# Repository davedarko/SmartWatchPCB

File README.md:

# SmartWatchPCB

work in progress, this is just setup to jump between computers n stuff.

I'm replacing the PCB of a cool watch from aliexpress

more on the project here
https://hackaday.io/project/180832-new-pcb-for-calculator-watch

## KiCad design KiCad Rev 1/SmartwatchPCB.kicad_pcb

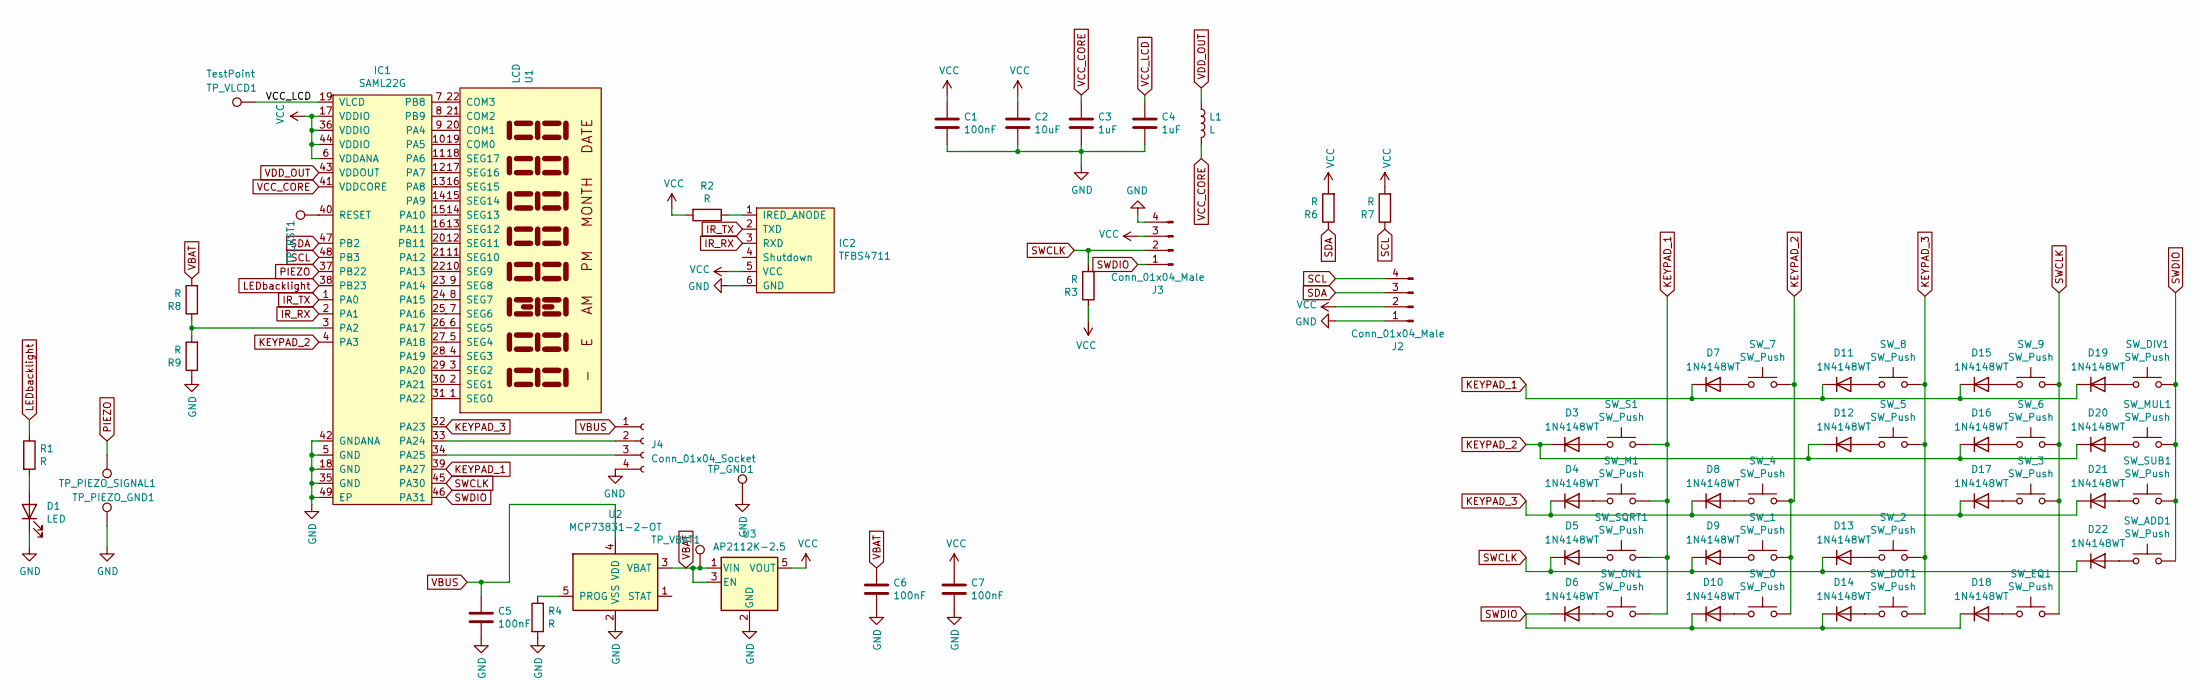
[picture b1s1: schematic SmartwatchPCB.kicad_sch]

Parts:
C1, C5, C6, C7: 100nF; C_0603_1608Metric
C2: 10uF; C_0603_1608Metric
C3, C4: 1uF; C_0603_1608Metric
D1: LED; LED_0603_1608Metric_Castellated
D3, D4, D5, D6, D7, D8, D9, D10, D11, D12, D13, D14, D15, D16, D17, D18, D19, D20, D21, D22: 1N4148WT; D_SOD-523
IC1: SAML22G; QFN-48-1EP_7x7mm_P0.5mm_EP5.15x5.15mm
IC2: TFBS4711
J2: Conn_01x04_Male; JST_SH_SM04B-SRSS-TB_1x04-1MP_P1.00mm_Horizontal
J3: Conn_01x04_Male; PinHeader_1x04_P2.54mm_Vertical
J4: Conn_01x04_Socket; JST_SH_SM04B-SRSS-TB_1x04-1MP_P1.00mm_Horizontal
L1: L; L_0603_1608Metric
R1, R2, R3, R4, R6, R7, R8, R9: R; R_0603_1608Metric
SW_0, SW_1, SW_2, SW_3, SW_4, SW_5, SW_6, SW_7, SW_8, SW_9: SW_Push; button
SW_ADD1: SW_Push; button
SW_DIV1: SW_Push; button
SW_DOT1: SW_Push; button
SW_EQ1: SW_Push; button
SW_M1: SW_Push; button
SW_MUL1: SW_Push; button
SW_ON1: SW_Push; button
SW_S1: SW_Push; button
SW_SQRT1: SW_Push; button
SW_SUB1: SW_Push; button
TP_GND1: TestPoint; TestPoint_Pad_D1.5mm
TP_PIEZO_GND1: TestPoint; TestPoint_Pad_D1.5mm
TP_PIEZO_SIGNAL1: TestPoint; TestPoint_Pad_D1.5mm
TP_RST1: TestPoint; TestPoint_Pad_D1.5mm
TP_VBAT1: TestPoint; TestPoint_Pad_D1.5mm
TP_VLCD1: TestPoint; TestPoint_Pad_D1.5mm
U1: LCD; display_MOUNT
U2: MCP73831-2-OT; SOT-23-5
U3: AP2112K-2.5; SOT-23-5

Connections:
GND: C1.2, C2.2, C3.2, C4.2, C5.2, C6.2, C7.2, D1.1 (K), IC1.5 (GND), IC1.18 (GND), IC1.35 (GND), IC1.42 (GNDANA), IC1.49 (EP), IC2.6 (GND), J2.1, J3.4, J4.4, R4.2, R9.1, TP_GND1.1, TP_PIEZO_GND1.1, U2.2 (VSS), U3.2 (GND)
IR_RX: IC1.2 (PA1), IC2.3 (RXD)
IR_TX: IC1.1 (PA0), IC2.2 (TXD)
KEYPAD_1: D7.1 (K), D11.1 (K), D15.1 (K), D19.1 (K), IC1.39 (PA27), SW_M1.2, SW_ON1.2, SW_S1.2, SW_SQRT1.2
KEYPAD_2: D3.1 (K), D12.1 (K), D16.1 (K), D20.1 (K), IC1.4 (PA3), SW_0.2, SW_1.2, SW_4.2, SW_7.2
KEYPAD_3: D4.1 (K), D8.1 (K), D17.1 (K), D21.1 (K), IC1.32 (PA23), SW_2.2, SW_5.2, SW_8.2, SW_DOT1.2
LEDbacklight: IC1.38 (PB23), R1.1
unnamed: D1.2 (A), R1.2
unnamed: D3.2 (A), SW_S1.1
unnamed: D4.2 (A), SW_M1.1
unnamed: D5.2 (A), SW_SQRT1.1
unnamed: D6.2 (A), SW_ON1.1
unnamed: D7.2 (A), SW_7.1
unnamed: D8.2 (A), SW_4.1
unnamed: D9.2 (A), SW_1.1
unnamed: D10.2 (A), SW_0.1
unnamed: D11.2 (A), SW_8.1
unnamed: D12.2 (A), SW_5.1
unnamed: D13.2 (A), SW_2.1
unnamed: D14.2 (A), SW_DOT1.1
unnamed: D15.2 (A), SW_9.1
unnamed: D16.2 (A), SW_6.1
unnamed: D17.2 (A), SW_3.1
unnamed: D18.2 (A), SW_EQ1.1
unnamed: D19.2 (A), SW_DIV1.1
unnamed: D20.2 (A), SW_MUL1.1
unnamed: D21.2 (A), SW_SUB1.1
unnamed: D22.2 (A), SW_ADD1.1
unnamed: IC1.3 (PA2), R8.1, R9.2
unnamed: IC1.9 (PA4), U1.20 (COM1)
unnamed: IC1.10 (PA5), U1.19 (COM0)
unnamed: IC1.11 (PA6), U1.18 (SEG17)
unnamed: IC1.12 (PA7), U1.17 (SEG16)
unnamed: IC1.13 (PA8), U1.16 (SEG15)
unnamed: IC1.14 (PA9), U1.15 (SEG14)
unnamed: IC1.15 (PA10), U1.14 (SEG13)
unnamed: IC1.16 (PA11), U1.13 (SEG12)
unnamed: IC1.21 (PA12), U1.11 (SEG10)
unnamed: IC1.22 (PA13), U1.10 (SEG9)
unnamed: IC1.23 (PA14), U1.9 (SEG8)
unnamed: IC1.24 (PA15), U1.8 (SEG7)
unnamed: IC1.25 (PA16), U1.7 (SEG6)
unnamed: IC1.26 (PA17), U1.6 (SEG5)
unnamed: IC1.27 (PA18), U1.5 (SEG4)
unnamed: IC1.28 (PA19), U1.4 (SEG3)
unnamed: IC1.29 (PA20), U1.3 (SEG2)
unnamed: IC1.30 (PA21), U1.2 (SEG1)
unnamed: IC1.31 (PA22), U1.1 (SEG0)
unnamed: IC1.33 (PA24), J4.2
unnamed: IC1.34 (PA25), J4.3
unnamed: IC1.7 (PB8), U1.22 (COM3)
unnamed: IC1.8 (PB9), U1.21 (COM2)
unnamed: IC1.20 (PB11), U1.12 (SEG11)
unnamed: IC1.40 (RESET), TP_RST1.1
unnamed: IC2.1 (IRED_ANODE), R2.1
unnamed: R4.1, U2.5 (PROG)
PIEZO: IC1.37 (PB22), TP_PIEZO_SIGNAL1.1
SCL: IC1.48 (PB3), J2.4, R7.1
SDA: IC1.47 (PB2), J2.3, R6.1
SWCLK: D5.1 (K), D9.1 (K), D13.1 (K), D22.1 (K), IC1.45 (PA30), J3.2, R3.2, SW_3.2, SW_6.2, SW_9.2, SW_EQ1.2
SWDIO: D6.1 (K), D10.1 (K), D14.1 (K), D18.1 (K), IC1.46 (PA31), J3.1, SW_ADD1.2, SW_DIV1.2, SW_MUL1.2, SW_SUB1.2
VBAT: C6.1, R8.2, TP_VBAT1.1, U2.3 (VBAT), U3.1 (VIN), U3.3 (EN)
VBUS: C5.1, J4.1, U2.4 (VDD)
VCC: C1.1, C2.1, C7.1, IC1.6 (VDDANA), IC1.17 (VDDIO), IC1.36 (VDDIO), IC1.44 (VDDIO), IC2.5 (VCC), J2.2, J3.3, R2.2, R3.1, R6.2, R7.2, U3.5 (VOUT)
VCC_CORE: C3.1, IC1.41 (VDDCORE), L1.2
VCC_LCD: C4.1, IC1.19 (VLCD), TP_VLCD1.1
VDD_OUT: IC1.43 (VDDOUT), L1.1

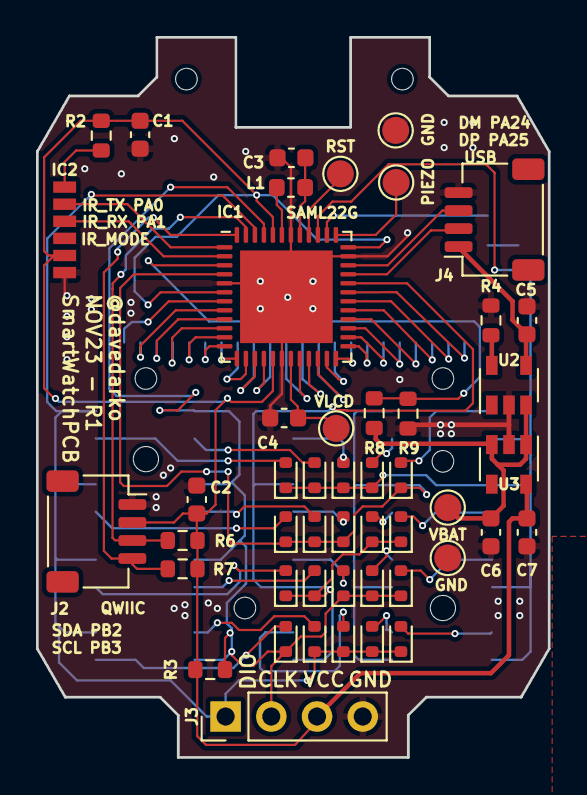
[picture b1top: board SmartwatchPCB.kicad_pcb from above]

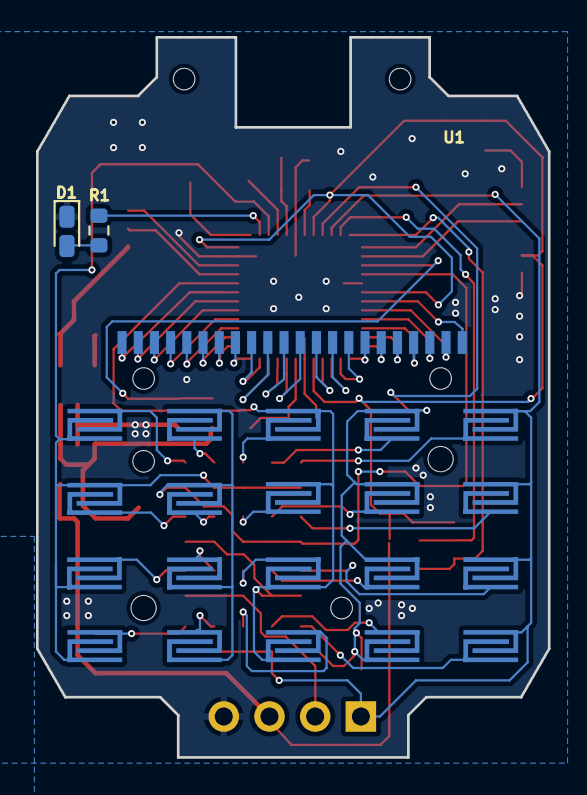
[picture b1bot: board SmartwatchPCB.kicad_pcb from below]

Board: 2 copper layers, 28.4 x 40.0 mm, 71 parts (23 on the bottom side), 67 nets.

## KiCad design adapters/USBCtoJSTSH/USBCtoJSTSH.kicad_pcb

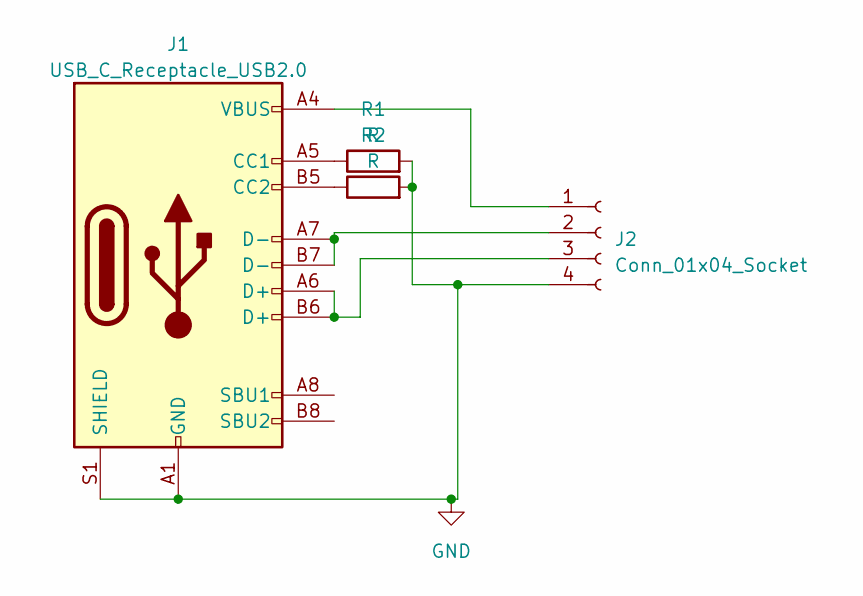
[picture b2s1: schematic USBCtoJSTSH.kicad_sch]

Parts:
J1: USB_C_Receptacle_USB2.0; USB_C_Receptacle_HRO_TYPE-C-31-M-12
J2: Conn_01x04_Socket; JST_SH_BM04B-SRSS-TB_1x04-1MP_P1.00mm_Vertical
R1, R2: R; R_0603_1608Metric_Pad0.98x0.95mm_HandSolder

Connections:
GND: J1.A1 (GND), J1.A12 (GND), J1.B1 (GND), J1.B12 (GND), J1.S1 (SHIELD), J2.4, R1.2, R2.2
unnamed: J1.A5 (CC1), R1.1
unnamed: J1.B5 (CC2), R2.1
unnamed: J1.A4 (VBUS), J1.A9 (VBUS), J1.B4 (VBUS), J1.B9 (VBUS), J2.1
unnamed: J1.A7 (D-), J1.B7 (D-), J2.2
unnamed: J1.A6 (D+), J1.B6 (D+), J2.3

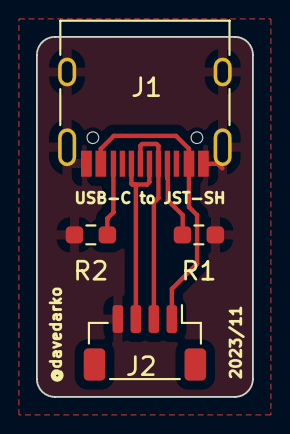
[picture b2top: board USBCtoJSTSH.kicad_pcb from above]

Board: 2 copper layers, 12.0 x 20.0 mm, 4 parts (0 on the bottom side), 6 nets.

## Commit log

2021-07-21 uploading resources
2021-07-21 uploading KiCad design files
2021-07-24 drafting and pinouts
2021-07-25 added button and lcd parts and sprinkled them
2021-08-02 anything to commit?
2021-08-02 started to wire up things
2021-08-03 more routing and footprint updates
2021-08-03 deleted unnecessary files
2021-08-03 removed scans from svg file
2021-09-11 added pdf to gitignore bc local datasheets
2021-09-11 footprint and symbol libraries updated
2021-09-11 moved IC, more wiring
2021-09-11 close to ordering first version
2021-09-12 swapped IR MODE to BAT ANALOG IN
2021-09-13 gerbering
2021-09-13 not sure what happened here
2023-11-16 revision 1 and adapter
